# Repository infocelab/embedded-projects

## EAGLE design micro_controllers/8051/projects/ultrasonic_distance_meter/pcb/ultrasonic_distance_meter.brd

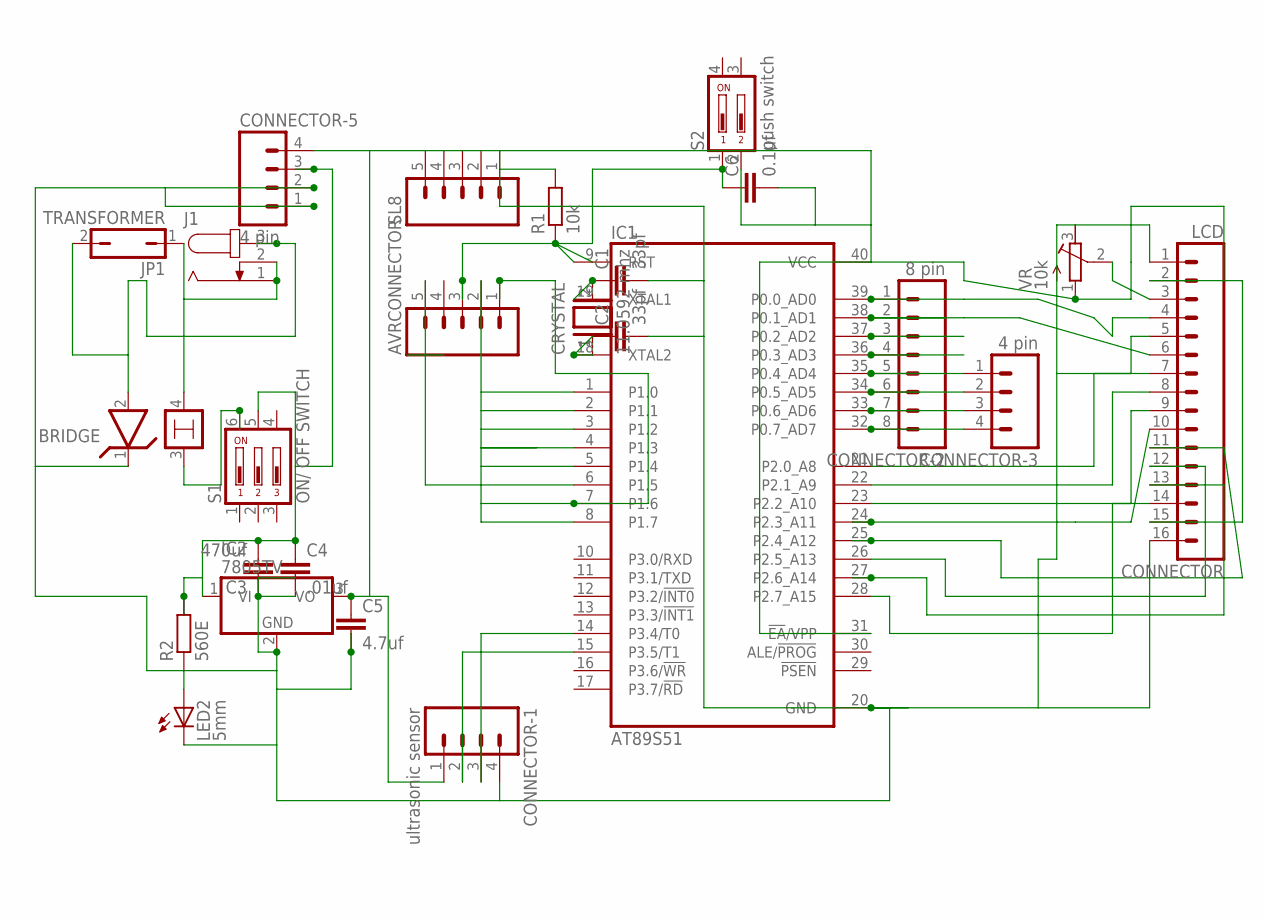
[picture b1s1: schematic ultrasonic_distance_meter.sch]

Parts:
AVRCONNECTOR: M05; 05P
BRIDGE: LM399H; TO39/4
C1, C2: 33pf; C025-024X044
C3: 470uf; C5B7.2
C4: .01uf; C2.5-3
C5: 4.7uf; C2.5-3
C6: 0.1uf; C2.5-6
CONNECTOR: LCD; 16P
CONNECTOR-1: ultrasonic sensor; 04P
CONNECTOR-2: 8 pin; 08P
CONNECTOR-3, CONNECTOR-5: 4 pin; 04P
CRYSTAL: 11.0592 mhz; QS
IC1: AT89S51; DIL40
IC2: 7805TV; TO220V
J1: JACK-PLUG0; SPC4077
JP1: TRANSFORMER; JP1
LED2: 5mm; LED5MM
R1: 10k; 0204/7
R2: 560E; 0204/7
S1: ON/ OFF SWITCH; DA-03
S2: push switch; DP-02
SL8: M05; 05P
VR: 10k; RTRIM64P

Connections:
unnamed: C2.1, CRYSTAL.1, IC1.18 (XTAL2)
unnamed: C1.1, CRYSTAL.2, IC1.19 (XTAL1)
unnamed: CONNECTOR-1.2, IC1.15 (P3.5/T1)
unnamed: C3.2, C4.1, CONNECTOR-5.3, IC2.1 (VI), R2.2, S1.5
unnamed: BRIDGE.2, J1.3, JP1.2
unnamed: CONNECTOR-1.3, IC1.14 (P3.4/T0)
unnamed: AVRCONNECTOR.3, C6.1, IC1.9 (RST), R1.1, S2.1
unnamed: AVRCONNECTOR.1, IC1.7 (P1.6)
unnamed: BRIDGE.4, J1.1, J1.2, JP1.1
unnamed: CONNECTOR-2.3, IC1.37 (P0.2_AD2)
unnamed: CONNECTOR-2.4, IC1.36 (P0.3_AD3)
unnamed: CONNECTOR-2.5, CONNECTOR-3.1, IC1.35 (P0.4_AD4)
unnamed: CONNECTOR-2.6, CONNECTOR-3.2, IC1.34 (P0.5_AD5)
unnamed: CONNECTOR-2.7, CONNECTOR-3.3, IC1.33 (P0.6_AD6)
unnamed: CONNECTOR-2.8, CONNECTOR-3.4, IC1.32 (P0.7_AD7)
unnamed: CONNECTOR.7, IC1.21 (P2.0_A8)
unnamed: CONNECTOR.8, IC1.22 (P2.1_A9)
unnamed: CONNECTOR.9, IC1.23 (P2.2_A10)
unnamed: CONNECTOR.12, IC1.26 (P2.5_A13)
unnamed: CONNECTOR.3, VR.2 (S)
unnamed: C5.1, C6.2, CONNECTOR.2, CONNECTOR.15, CONNECTOR-1.1, CONNECTOR-5.4, IC1.31 (!EA!/VPP), IC1.40 (VCC), IC2.3 (VO), S2.2, VR.1 (E)
unnamed: BRIDGE.1, C1.2, C2.2, C3.1, C4.2, C5.2, CONNECTOR.1, CONNECTOR.5, CONNECTOR.16, CONNECTOR-1.4, CONNECTOR-5.1, CONNECTOR-5.2, IC1.20 (GND), IC2.2 (GND), LED2.K (C), R1.2, SL8.1, VR.3 (A)
unnamed: AVRCONNECTOR.5, IC1.6 (P1.5)
unnamed: LED2.A, R2.1
unnamed: AVRCONNECTOR.2, IC1.8 (P1.7)
unnamed: BRIDGE.3, S1.6
unnamed: CONNECTOR.6, CONNECTOR-2.2, IC1.38 (P0.1_AD1)
unnamed: CONNECTOR.10, IC1.24 (P2.3_A11)
unnamed: CONNECTOR.11, IC1.25 (P2.4_A12)
unnamed: CONNECTOR.13, IC1.27 (P2.6_A14)
unnamed: CONNECTOR.14, IC1.28 (P2.7_A15)
unnamed: CONNECTOR.4, CONNECTOR-2.1, IC1.39 (P0.0_AD0)

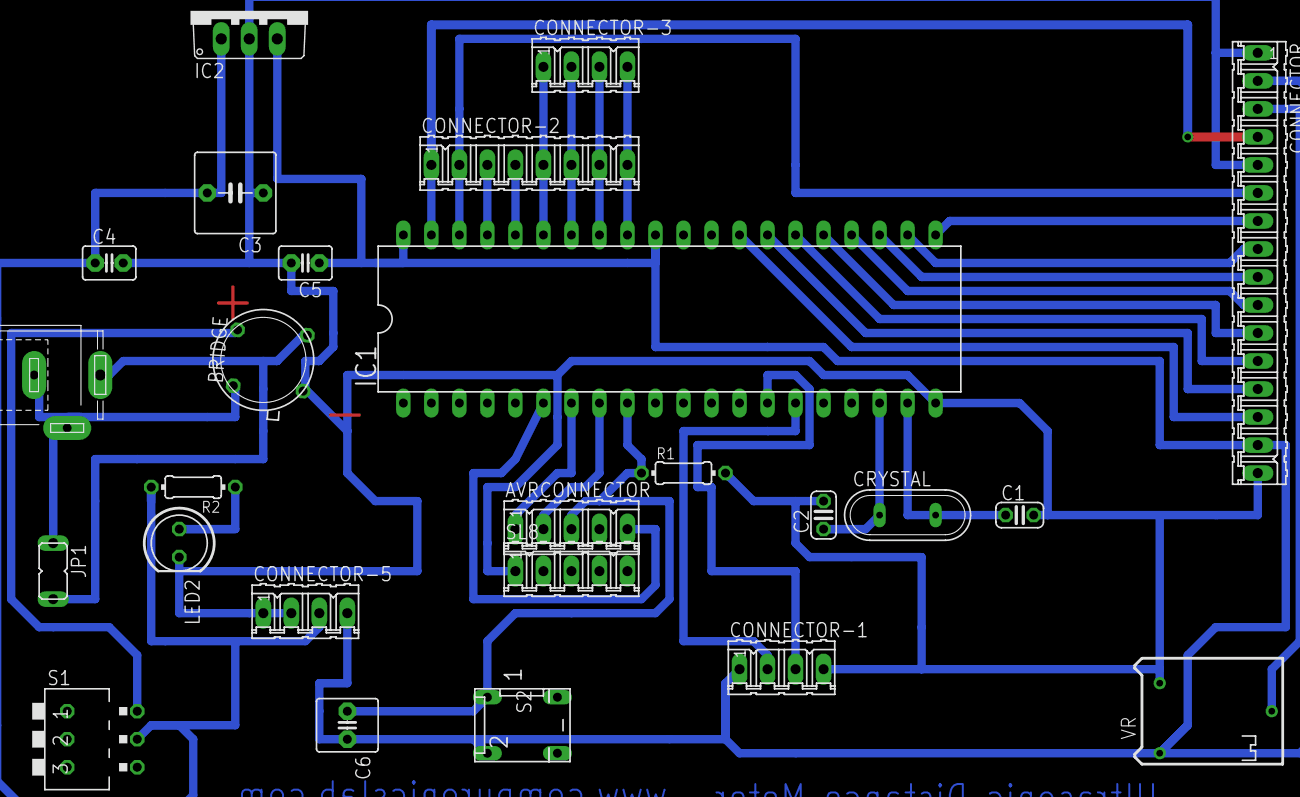
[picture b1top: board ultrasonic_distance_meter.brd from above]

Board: 2 copper layers, 25 parts (0 on the bottom side), 32 nets.

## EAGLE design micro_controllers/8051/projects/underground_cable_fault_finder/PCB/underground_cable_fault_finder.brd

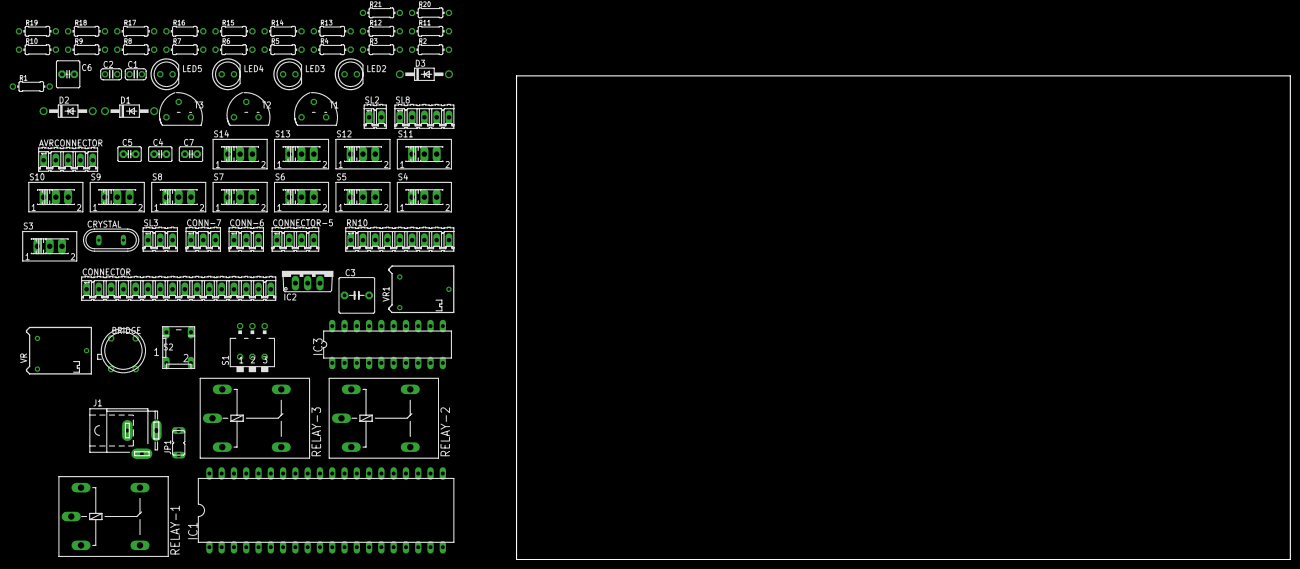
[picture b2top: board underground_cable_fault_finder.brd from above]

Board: 2 copper layers, 73 parts (0 on the bottom side), 70 nets, no tracks yet.

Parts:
AVRCONNECTOR: 05P
BRIDGE: TO39/4
C1, C2: 33pf; C025-024X044
C3: 470uf; C5B7.2
C4: .01uf; C2.5-3
C5: 4.7uf; C2.5-3
C6: 0.1uf; C2.5-6
C7: 150pf; C2.5-3
CONN-6, CONN-7: 3 pin; 03P
CONNECTOR: LCD; 16P
CONNECTOR-5: 4 pin; 04P
CRYSTAL: 11.0592 mhz; QS
D1, D2, D3: 1N4007; DO41-10
IC1: AT89S51; DIL40
IC2: 7805TV; TO220V
IC3: adc804; DIL20
J1: SPC4077
JP1: TRANSFORMER; JP1
LED2: 5mm; LED5MM
LED3, LED4, LED5: 5MM; LED5MM
R1, R3, R4, R5, R6, R7, R8, R9, R10, R11, R12, R13, R14, R15: 10k; 0204/7
R2: 560E; 0204/7
R16, R17, R21: 1K; 0204/7
R18, R19, R20: 5.6K; 0204/7
RELAY-1, RELAY-2, RELAY-3: 12V; G5LE
RN10: 10 k; 09P
S1: ON/ OFF SWITCH; DA-03
S2: push switch; DP-02
S3, S4, S5, S6, S7, S8, S9, S10, S11, S12, S13, S14: 255SB
SL2: 02P
SL3: LM35; 03P
SL8: 05P
T1, T2, T3: BC547; TO92
VR, VR1: 10k; RTRIM64P

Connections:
unnamed: C2.1, CRYSTAL.1, IC1.18
unnamed: C1.1, CRYSTAL.2, IC1.19
unnamed: BRIDGE.1, C1.2, C2.2, C3.1, C4.2, C5.2, C7.2, CONNECTOR.1, CONNECTOR.5, CONNECTOR.16, CONNECTOR-5.1, CONNECTOR-5.2, IC1.20, IC2.2, IC3.1, IC3.2, IC3.7, IC3.8, IC3.10, LED2.K, R1.2, RELAY-1.S, RELAY-2.S, RELAY-3.S, S5.1, S10.1, S14.1, SL2.2, SL3.3, SL8.1, T1.1, T2.1, T3.1, VR.3, VR1.3
unnamed: C3.2, C4.1, CONN-6.1, CONN-6.2, CONN-6.3, CONNECTOR-5.3, D1.C, D2.C, D3.C, IC2.1, R2.2, R16.2, R17.2, R21.1, RELAY-1.1, RELAY-2.1, RELAY-3.1, S1.5
unnamed: BRIDGE.2, J1.3, JP1.2
unnamed: IC1.1, IC3.18
unnamed: IC1.2, IC3.17
unnamed: IC1.3, IC3.16
unnamed: IC1.4, IC3.15
unnamed: IC1.5, IC3.14
unnamed: AVRCONNECTOR.5, IC1.6, IC3.13
unnamed: AVRCONNECTOR.1, IC1.7, IC3.12
unnamed: AVRCONNECTOR.3, C6.1, IC1.9, R1.1, S2.1
unnamed: C5.1, C6.2, CONN-7.1, CONN-7.2, CONN-7.3, CONNECTOR.2, CONNECTOR.15, CONNECTOR-5.4, IC1.31, IC1.40, IC2.3, IC3.20, RN10.1, S2.2, SL2.1, SL3.1, SL8.2, SL8.3, SL8.4, SL8.5, VR.1, VR1.1
unnamed: BRIDGE.4, J1.1, J1.2, JP1.1
unnamed: IC3.19, R3.2
unnamed: C7.1, IC3.4, R3.1
unnamed: IC3.6, SL3.2
unnamed: S3.3, S4.3, S5.3, S6.3, S7.3, S8.3, S9.3, S10.3, S11.3, S12.3, S13.3, S14.3
unnamed: R4.2, S8.2
unnamed: R5.2, S3.2
unnamed: IC3.9, VR1.2
unnamed: IC1.37, RN10.4
unnamed: IC1.36, R18.2, RN10.5
unnamed: IC1.34, RN10.7
unnamed: IC1.33, RN10.8
unnamed: IC1.32, RN10.9
unnamed: CONNECTOR.7, IC1.21
unnamed: CONNECTOR.8, IC1.22
unnamed: CONNECTOR.9, IC1.23
unnamed: R5.1, S8.1
unnamed: R6.2, S4.2
unnamed: CONNECTOR.12, IC1.26
unnamed: R6.1, S3.1
unnamed: R7.2, S5.2
unnamed: CONNECTOR.3, VR.2
unnamed: R9.1, S9.1
unnamed: R8.2, S9.2
unnamed: R9.2, S6.2
unnamed: LED2.A, R2.1
unnamed: R10.1, S6.1
unnamed: AVRCONNECTOR.2, IC1.8
unnamed: BRIDGE.3, S1.6
unnamed: CONNECTOR.6, IC1.38, RN10.3
unnamed: R11.1, S7.1
unnamed: CONNECTOR.10, IC1.24
unnamed: CONNECTOR.11, IC1.25
unnamed: CONNECTOR.13, IC1.27
unnamed: CONNECTOR.14, IC1.28
unnamed: R12.2, S11.2
unnamed: CONNECTOR.4, IC1.39, RN10.2
unnamed: R13.2, S12.2
unnamed: R14.2, S13.2
unnamed: R13.1, S11.1
unnamed: R14.1, S12.1
unnamed: R15.1, S13.1
unnamed: D1.A, LED3.K, RELAY-1.2, T2.3
unnamed: R19.1, T1.2
unnamed: R18.1, T2.2
unnamed: LED3.A, R17.1
unnamed: LED4.A, R16.1
unnamed: R8.1, RELAY-1.P
unnamed: R12.1, RELAY-2.P
unnamed: D2.A, LED4.K, RELAY-2.2, T1.3
unnamed: D3.A, LED5.K, RELAY-3.2, T3.3
unnamed: R20.1, T3.2
unnamed: LED5.A, R21.2
unnamed: R4.1, RELAY-3.P
unnamed: IC1.35, R19.2, RN10.6
unnamed: R7.1, S4.1

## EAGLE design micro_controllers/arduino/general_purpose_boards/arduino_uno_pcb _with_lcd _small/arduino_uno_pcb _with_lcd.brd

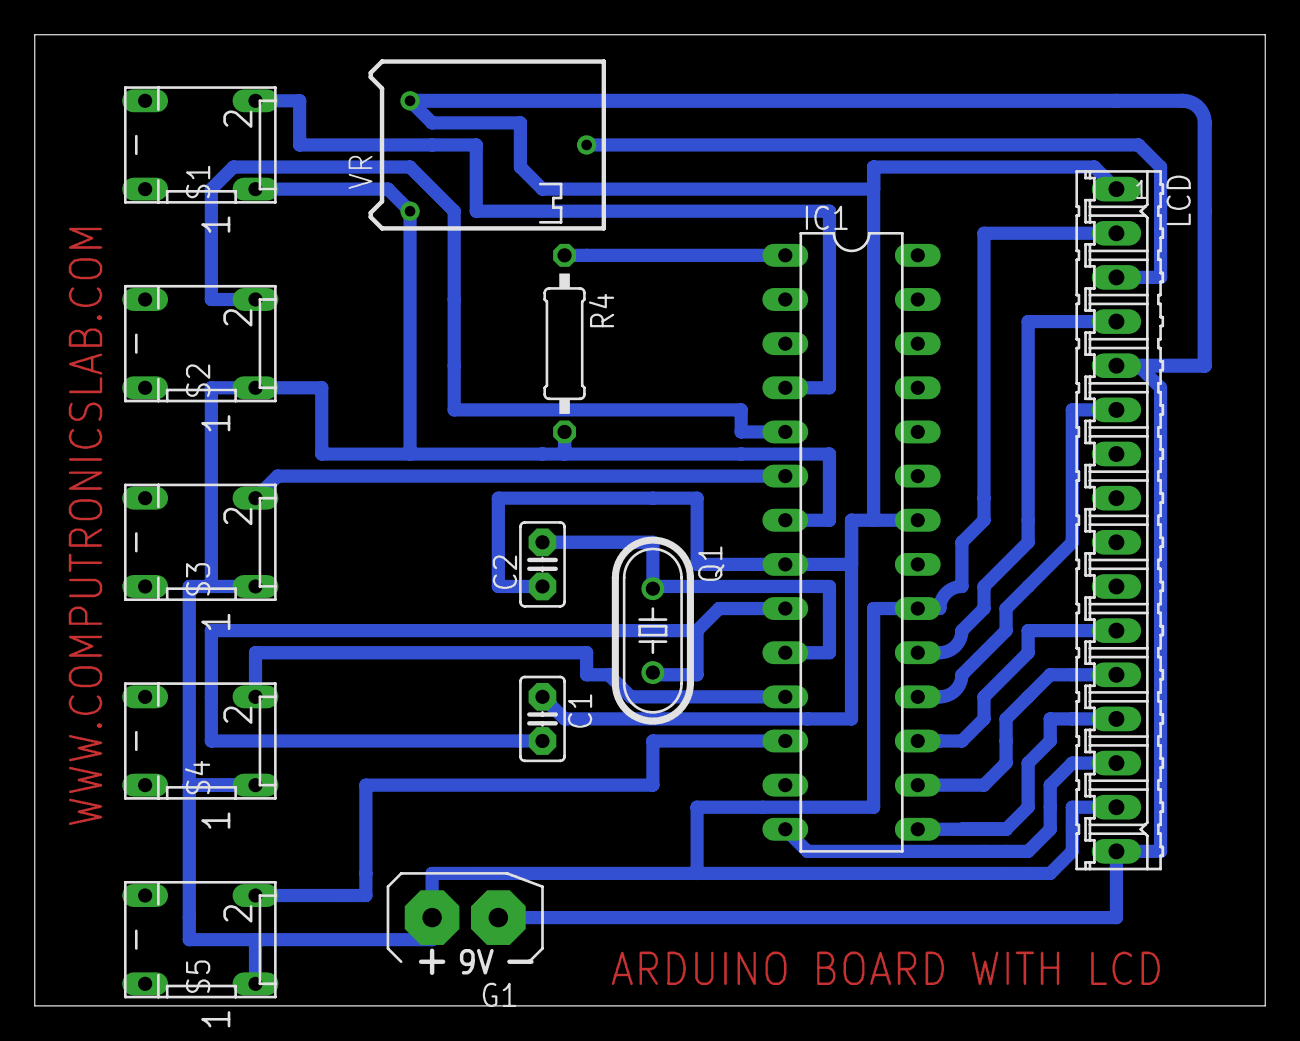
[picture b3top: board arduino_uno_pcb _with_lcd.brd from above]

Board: 2 copper layers, 70.8 x 55.9 mm, 13 parts (0 on the bottom side), 17 nets.

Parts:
C1, C2: 22pf; C2.5-2
G1: AB9V
IC1: ATMEGA328; DIL28-3
LCD: 16P
Q1: 16MHZ; HC49/S
R4: 10K; 0207/10
S1, S2, S3, S4, S5: DP-02
VR: 100k; RTRIM64P

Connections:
unnamed: C1.2, IC1.9, Q1.2
unnamed: C2.2, IC1.10, Q1.1
unnamed: G1.+, IC1.7, IC1.20, LCD.2, LCD.15, R4.2, S1.1, S2.1, S3.1, S4.1, S5.1, VR.1
unnamed: IC1.11, S4.2
unnamed: IC1.4, S1.2
unnamed: IC1.5, S2.2
unnamed: IC1.6, S3.2
unnamed: IC1.12, S5.2
unnamed: LCD.3, VR.2
unnamed: IC1.19, LCD.4
unnamed: IC1.18, LCD.6
unnamed: IC1.17, LCD.11
unnamed: IC1.16, LCD.12
unnamed: IC1.15, LCD.13
unnamed: C1.1, C2.1, G1.-, IC1.8, IC1.22, LCD.1, LCD.5, LCD.16, VR.3
unnamed: IC1.14, LCD.14
unnamed: IC1.1, R4.1

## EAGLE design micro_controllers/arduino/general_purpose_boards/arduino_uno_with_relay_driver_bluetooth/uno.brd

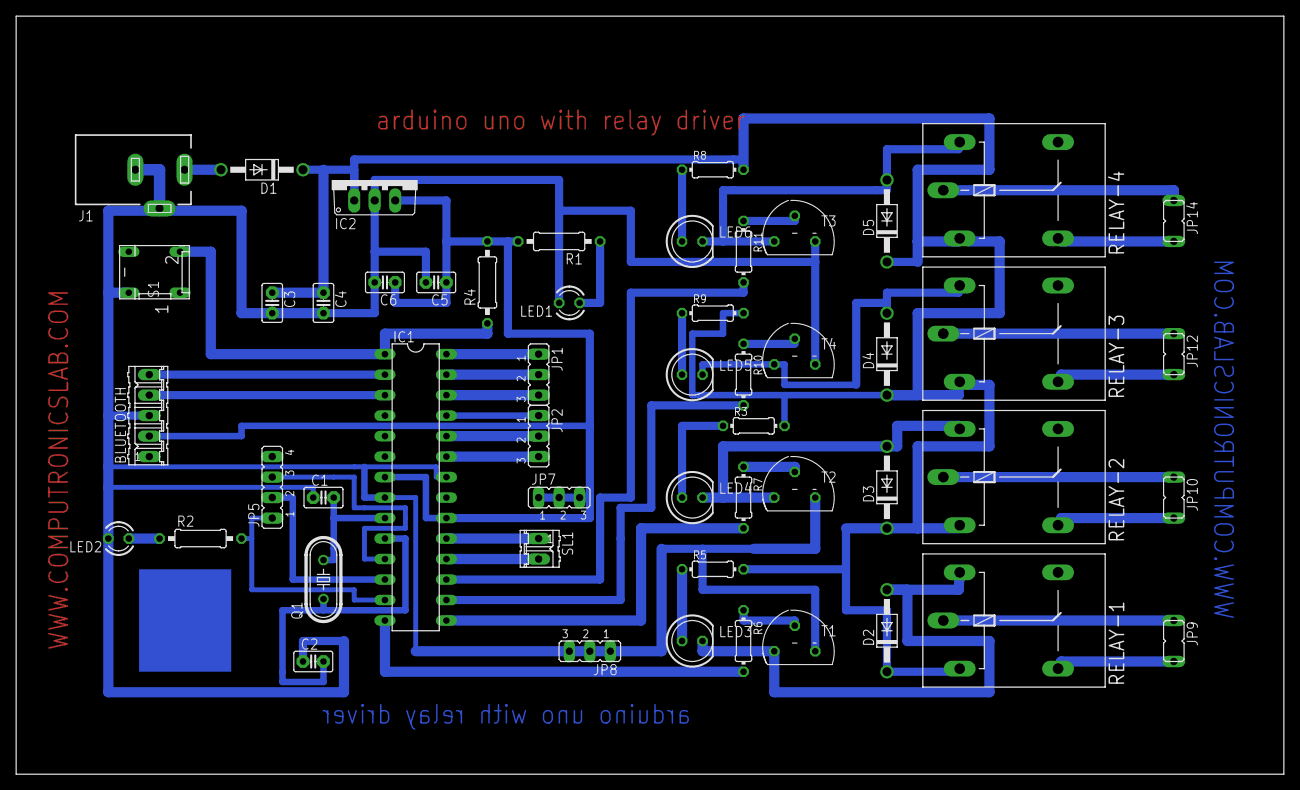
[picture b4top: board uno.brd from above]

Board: 2 copper layers, 157.2 x 94.0 mm, 52 parts (0 on the bottom side), 46 nets.

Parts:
BLUETOOTH: 5 pin; 05P
C1, C2: 22pf; C2.5-2
C3: 100UF; C2.5-2
C4, C5: 0.1uf; C2.5-2
C6: 4.7uf; C2.5-2
D1, D2, D3, D4, D5: 1N4007; DO41-10
IC1: ATMEGA328; DIL28-3
IC2: 7805; TO220V
J1: DCJ0303
JP1, JP2, JP7, JP8: JP2
JP5: JP4
JP9, JP10, JP12, JP14: AC CONNECTOR; JP1
LED1, LED2: LED3MM
LED3, LED4, LED5, LED6: 5MM; LED5MM
Q1: 12MHZ; HC49/S
R1: 220R; 0207/10
R2: 330R; 0207/10
R3, R5, R8, R9: 1K; 0204/7
R4: 10K; 0207/10
R6, R7, R10, R11: 5.6K; 0204/7
RELAY-1, RELAY-2, RELAY-3, RELAY-4: 12V; G5LE
S1: DP-02
SL1: 02P
T1, T2, T3, T4: BC547; TO92

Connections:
unnamed: C1.2, IC1.9, Q1.2
unnamed: C2.2, IC1.10, Q1.1
unnamed: D1.A, J1.1
unnamed: BLUETOOTH.2, C5.1, C6.1, IC1.7, IC1.20, IC2.3, JP7.1, JP7.2, JP7.3, R1.2, R4.2
unnamed: IC1.18, SL1.2
unnamed: LED1.A, R1.1
unnamed: C3.1, C4.1, D1.C, D2.C, D3.C, D4.C, D5.C, IC2.1, R3.2, R5.2, R8.2, R9.2, RELAY-1.1, RELAY-2.1, RELAY-3.1, RELAY-4.1
unnamed: IC1.28, JP1.1
unnamed: IC1.27, JP1.2
unnamed: IC1.26, JP1.3
unnamed: IC1.25, JP2.1
unnamed: IC1.24, JP2.2
unnamed: IC1.23, JP2.3
unnamed: BLUETOOTH.5, IC1.2
unnamed: BLUETOOTH.4, IC1.3
unnamed: IC1.12, JP5.2
unnamed: IC1.11, JP5.3
unnamed: IC1.13, JP5.1, R2.2
unnamed: IC1.19, SL1.1
unnamed: D2.A, LED3.K, RELAY-1.2, T1.3
unnamed: R7.1, T2.2
unnamed: R6.1, T1.2
unnamed: IC1.1, R4.1, S1.2
unnamed: LED2.A, R2.1
unnamed: LED3.A, R5.1
unnamed: LED4.A, R3.1
unnamed: JP9.2, RELAY-1.S
unnamed: JP9.1, RELAY-1.P
unnamed: JP10.2, RELAY-2.S
unnamed: JP10.1, RELAY-2.P
unnamed: IC1.14, R6.2
unnamed: D3.A, LED4.K, RELAY-2.2, T2.3
unnamed: D4.A, LED5.K, RELAY-3.2, T4.3
unnamed: R11.1, T3.2
unnamed: R10.1, T4.2
unnamed: LED5.A, R9.1
unnamed: LED6.A, R8.1
unnamed: JP12.2, RELAY-3.S
unnamed: JP12.1, RELAY-3.P
unnamed: JP14.2, RELAY-4.S
unnamed: JP14.1, RELAY-4.P
unnamed: BLUETOOTH.3, C1.1, C2.1, C3.2, C4.2, C5.2, C6.2, IC1.8, IC1.22, IC2.2, J1.2, J1.3, JP8.1, JP8.2, JP8.3, LED1.K, LED2.K, S1.4, T1.1, T2.1, T3.1, T4.1
unnamed: IC1.16, R10.2
unnamed: IC1.17, R11.2
unnamed: D5.A, LED6.K, RELAY-4.2, T3.3
unnamed: IC1.15, R7.2

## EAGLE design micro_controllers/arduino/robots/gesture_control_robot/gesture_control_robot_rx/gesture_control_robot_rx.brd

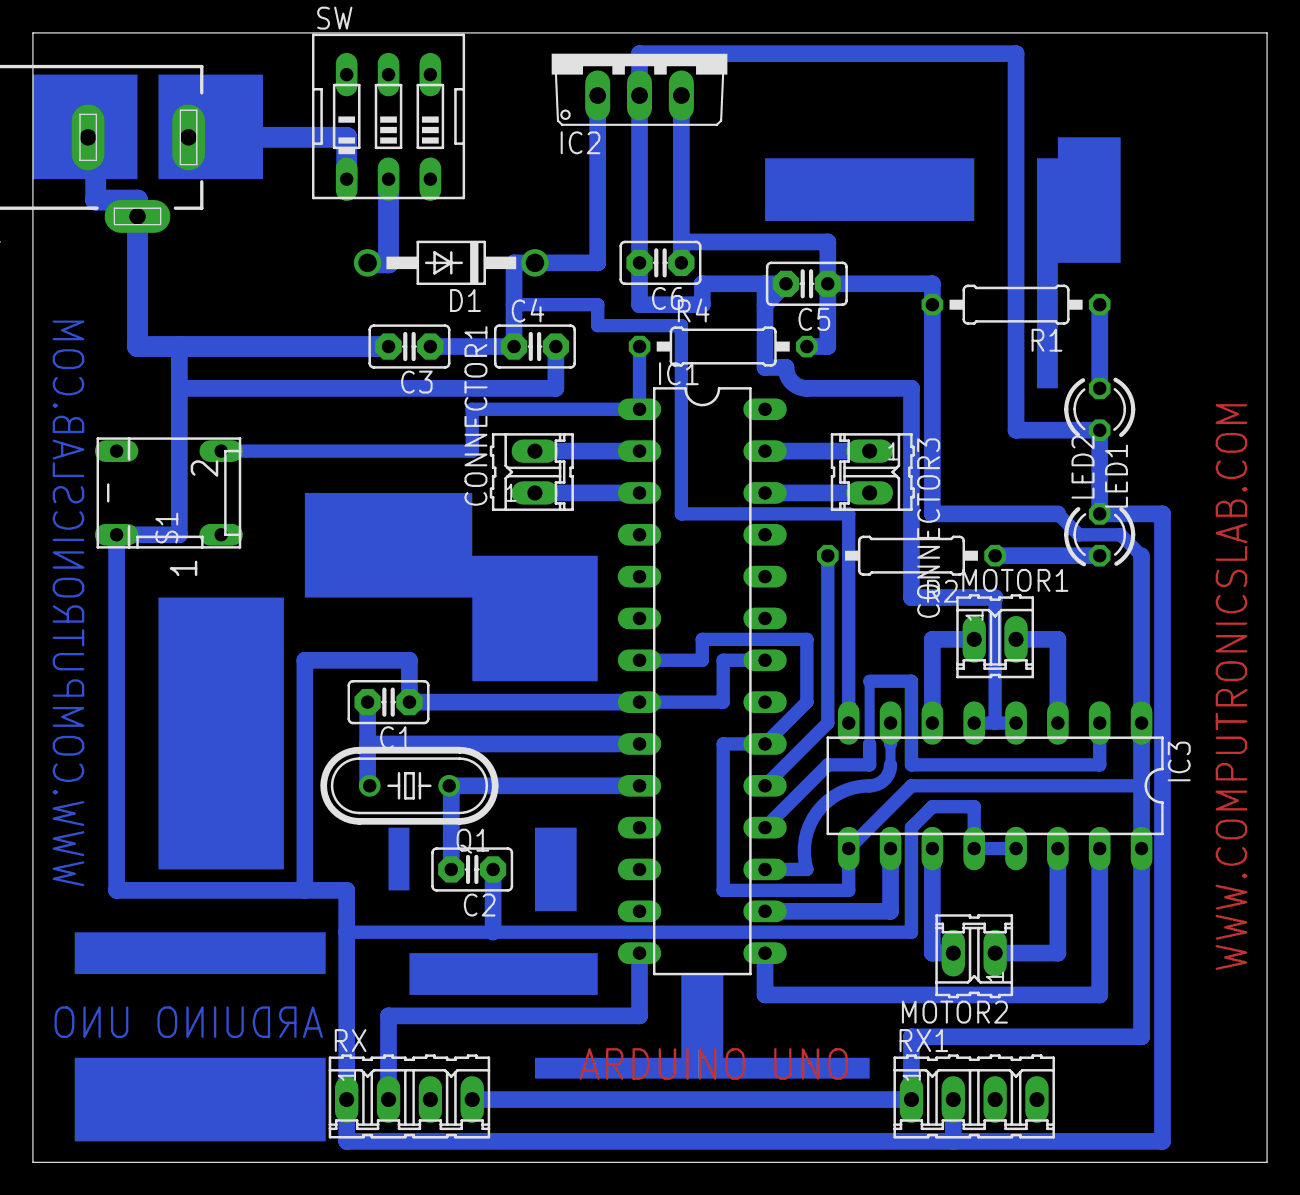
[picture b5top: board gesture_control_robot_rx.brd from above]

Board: 2 copper layers, 74.9 x 68.6 mm, 25 parts (0 on the bottom side), 24 nets.

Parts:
C1, C2: 22pf; C2.5-2
C3: 470uF; C2.5-2
C4, C5: 0.1uf; C2.5-2
C6: 4.7uf; C2.5-2
CONNECTOR1: 2 pin; 02P
CONNECTOR3: 02P
D1: 1N4007; DO41-10
IC1: ATMEGA328; DIL28-3
IC2: 7805; TO220V
IC3: L293D; DIL16
J1: DCJ0303
LED1, LED2: 3mm; LED3MM
MOTOR1, MOTOR2: 02P
Q1: 16MHZ; HC49/S
R1: 220R; 0207/10
R2: 330R; 0207/10
R4: 10K; 0207/10
RX, RX1: 04P
S1: push switch; DP-02
SW: on/of button; EDG-03

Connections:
unnamed: C1.2, IC1.9, Q1.2
unnamed: C2.2, IC1.10, Q1.1
unnamed: J1.1, SW.1
unnamed: C3.1, C4.1, D1.C, IC2.1, IC3.8
unnamed: C1.1, C2.1, C3.2, C4.2, C5.2, C6.2, IC1.8, IC1.22, IC2.2, IC3.4, IC3.5, IC3.12, IC3.13, J1.2, J1.3, LED1.K, LED2.K, RX.1, RX1.2, S1.4
unnamed: LED1.A, R1.1
unnamed: IC1.17, IC3.7
unnamed: CONNECTOR1.1, IC1.3
unnamed: CONNECTOR1.2, IC1.2
unnamed: CONNECTOR3.1, IC1.27
unnamed: CONNECTOR3.2, IC1.26
unnamed: IC1.14, RX.2
unnamed: IC1.18, IC3.2
unnamed: IC1.15, IC3.15
unnamed: D1.A, SW.2
unnamed: IC1.16, IC3.10
unnamed: IC3.14, MOTOR2.1
unnamed: IC1.19, R2.2
unnamed: IC3.11, MOTOR2.2
unnamed: IC1.1, R4.1, S1.2
unnamed: LED2.A, R2.1
unnamed: C5.1, C6.1, IC1.7, IC1.20, IC2.3, IC3.1, IC3.9, IC3.16, R1.2, R4.2, RX.4, RX1.1
unnamed: IC3.6, MOTOR1.1
unnamed: IC3.3, MOTOR1.2

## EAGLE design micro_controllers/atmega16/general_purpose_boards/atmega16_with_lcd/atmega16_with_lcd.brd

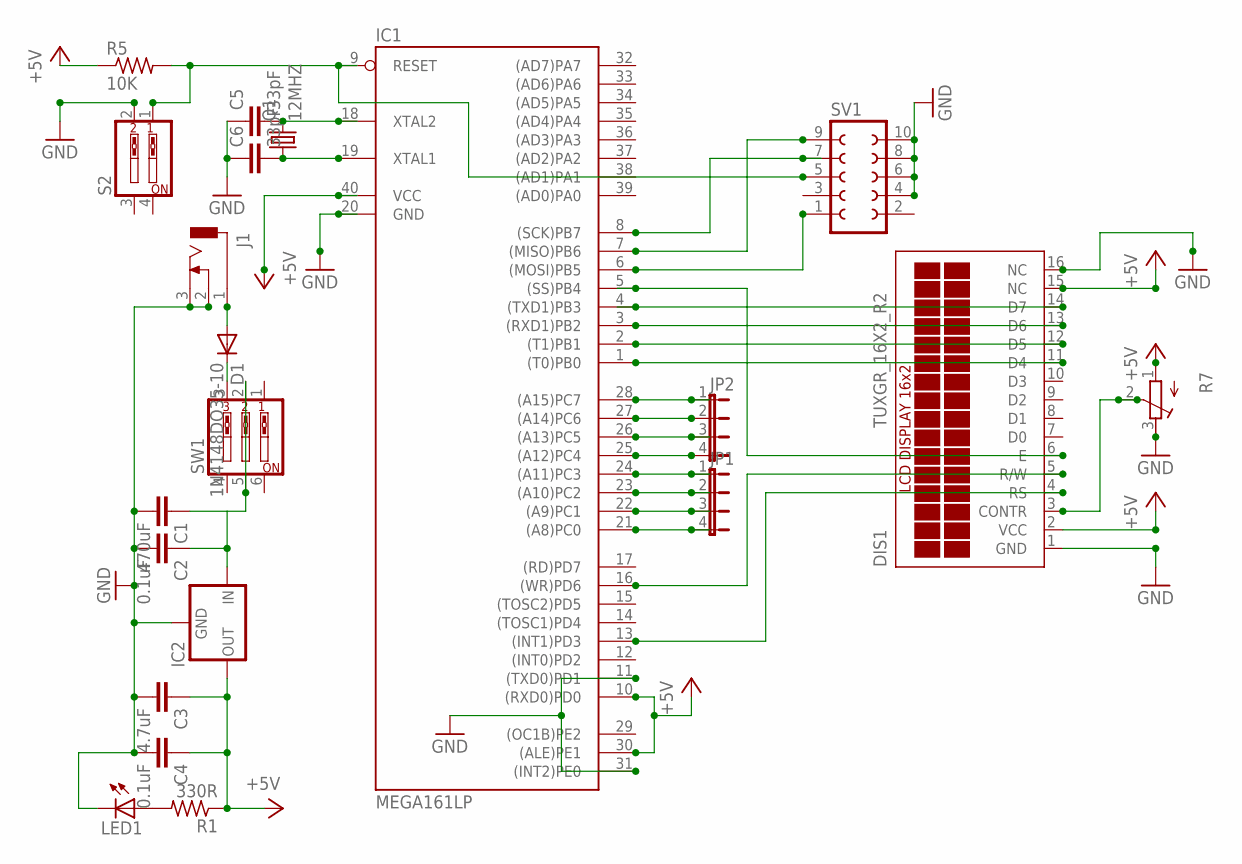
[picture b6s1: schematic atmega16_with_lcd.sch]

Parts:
C1: 470uF; C2.5-4
C2, C4: 0.1uF; C2.5-4
C3: 4.7uF; C2.5-4
C5, C6: 33pF; C2.5-4
D1: 1N4148DO35-10; DO35-10
DIS1: TUXGR_16X2_R2
IC1: MEGA161LP; DIL40
IC2: 78XXS
J1: DCJ0303
JP1, JP2: JP4E; JP4
LED1: LED_ELD260; LED_LD260
Q1: 12MHZ; HC49U-V
R1: 330R; 0204/7
R5: 10K; 0204/7
R7: R-TRIMM3339P; RTRIM3339P
S2: SW_DIP-2; EDG-02
SV1: FE05-2
SW1: SW_DIP-3; EDG-03

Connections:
+5V: C3.1, C4.1, DIS1.2 (VCC), DIS1.15 (NC), IC1.10 ((RXD0)PD0), IC1.30 ((ALE)PE1), IC1.40 (VCC), IC2.OUT, R1.1, R5.1, R7.1 (E)
GND: C1.2, C2.2, C3.2, C4.2, C5.1, C6.1, DIS1.1 (GND), DIS1.16 (NC), IC1.11 ((TXD0)PD1), IC1.20 (GND), IC1.31 ((INT2)PE0), IC2.GND, J1.2, J1.3, LED1.K (C), R7.3 (A), S2.2, SV1.4, SV1.6, SV1.8, SV1.10
unnamed: D1.A, J1.1
unnamed: IC1.28 ((A15)PC7), JP2.1
unnamed: C5.2, IC1.18 (XTAL2), Q1.2
unnamed: C6.2, IC1.19 (XTAL1), Q1.1
unnamed: LED1.A, R1.2
unnamed: IC1.9 (RESET), R5.2, S2.1, SV1.5
unnamed: DIS1.3 (CONTR), R7.2 (S)
unnamed: D1.C, SW1.3
unnamed: C1.1, C2.1, IC2.IN, SW1.2, SW1.5
unnamed: DIS1.11 (D4), IC1.1 ((T0)PB0)
unnamed: DIS1.12 (D5), IC1.2 ((T1)PB1)
unnamed: DIS1.13 (D6), IC1.3 ((RXD1)PB2)
unnamed: DIS1.14 (D7), IC1.4 ((TXD1)PB3)
unnamed: DIS1.4 (RS), IC1.13 ((INT1)PD3)
unnamed: DIS1.5 (R/W), IC1.16 ((WR)PD6)
unnamed: DIS1.6 (E), IC1.5 ((SS)PB4)
unnamed: IC1.27 ((A14)PC6), JP2.2
unnamed: IC1.26 ((A13)PC5), JP2.3
unnamed: IC1.25 ((A12)PC4), JP2.4
unnamed: IC1.24 ((A11)PC3), JP1.1
unnamed: IC1.23 ((A10)PC2), JP1.2
unnamed: IC1.22 ((A9)PC1), JP1.3
unnamed: IC1.21 ((A8)PC0), JP1.4
unnamed: IC1.6 ((MOSI)PB5), SV1.1
unnamed: IC1.7 ((MISO)PB6), SV1.9
unnamed: IC1.8 ((SCK)PB7), SV1.7

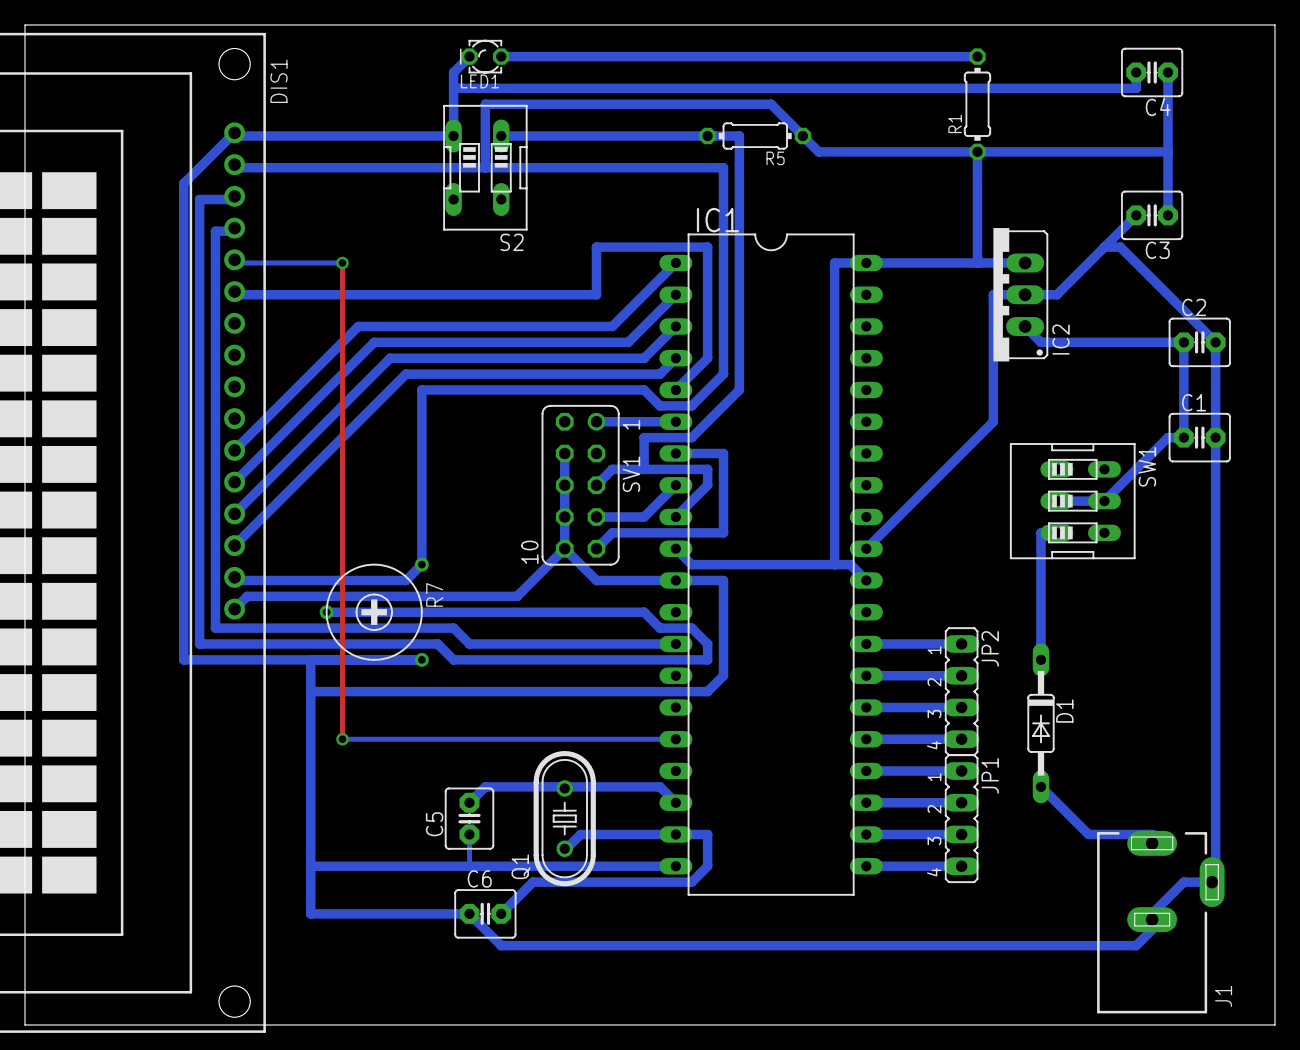
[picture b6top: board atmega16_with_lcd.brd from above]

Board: 2 copper layers, 100.0 x 80.0 mm, 21 parts (0 on the bottom side), 28 nets.
